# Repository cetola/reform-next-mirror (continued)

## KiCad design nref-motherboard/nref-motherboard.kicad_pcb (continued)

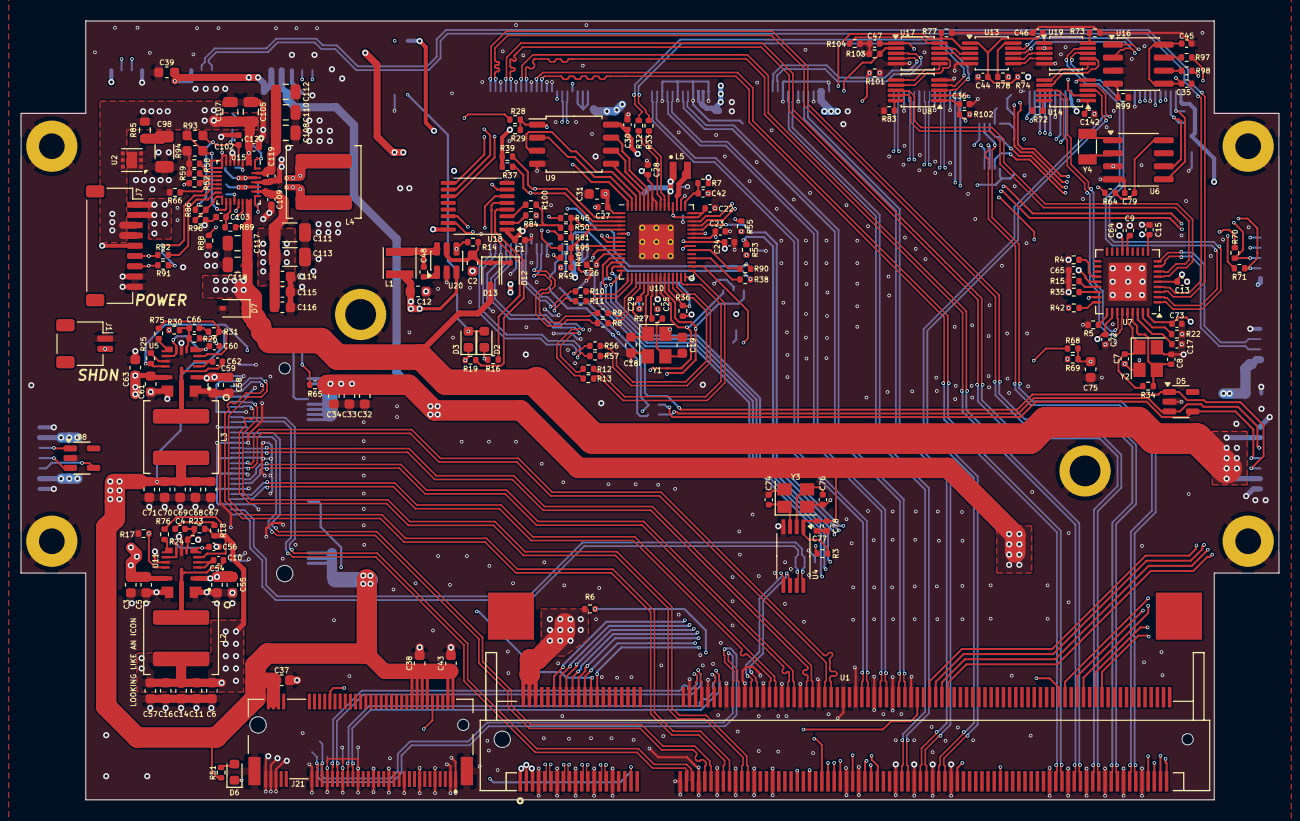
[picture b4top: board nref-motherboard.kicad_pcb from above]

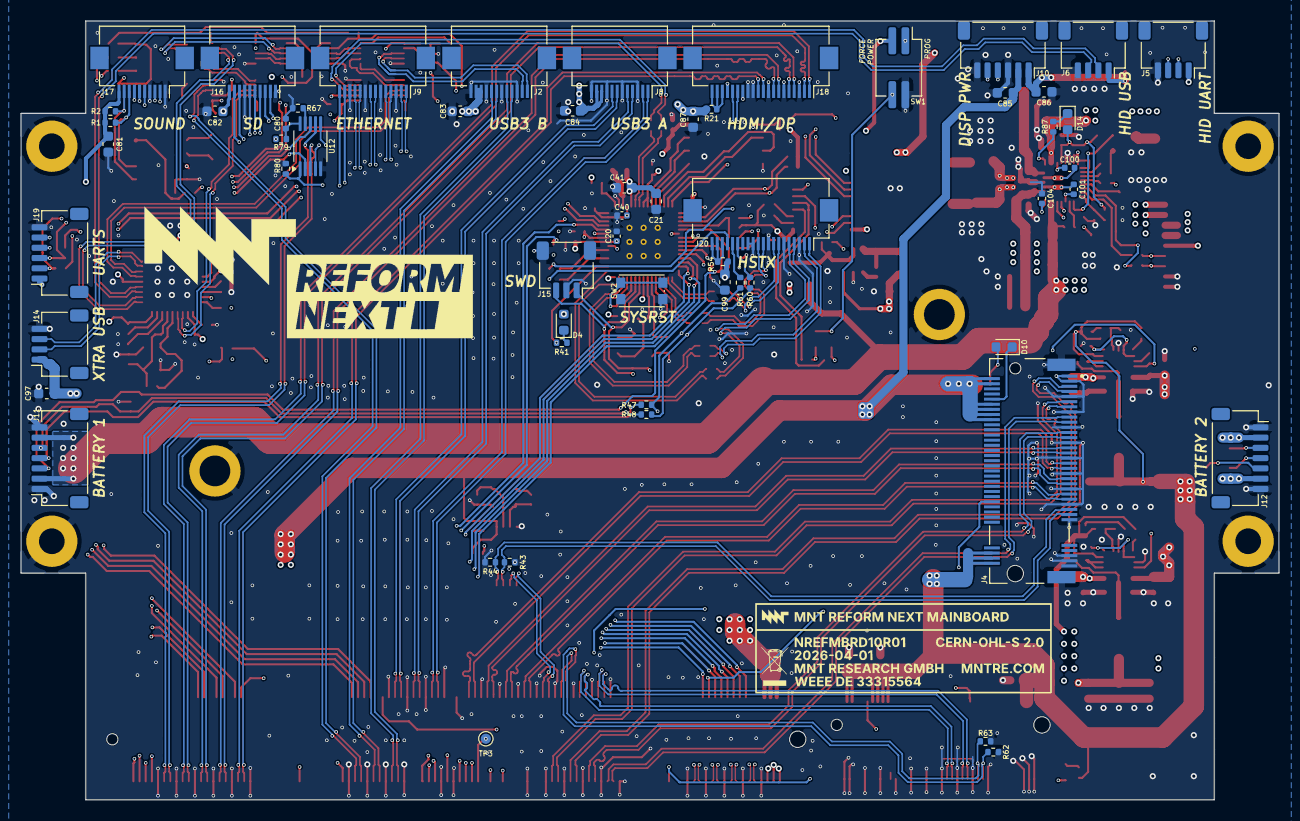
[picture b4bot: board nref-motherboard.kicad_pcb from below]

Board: 6 copper layers, 122.6 x 75.9 mm, 276 parts (60 on the bottom side), 267 nets.

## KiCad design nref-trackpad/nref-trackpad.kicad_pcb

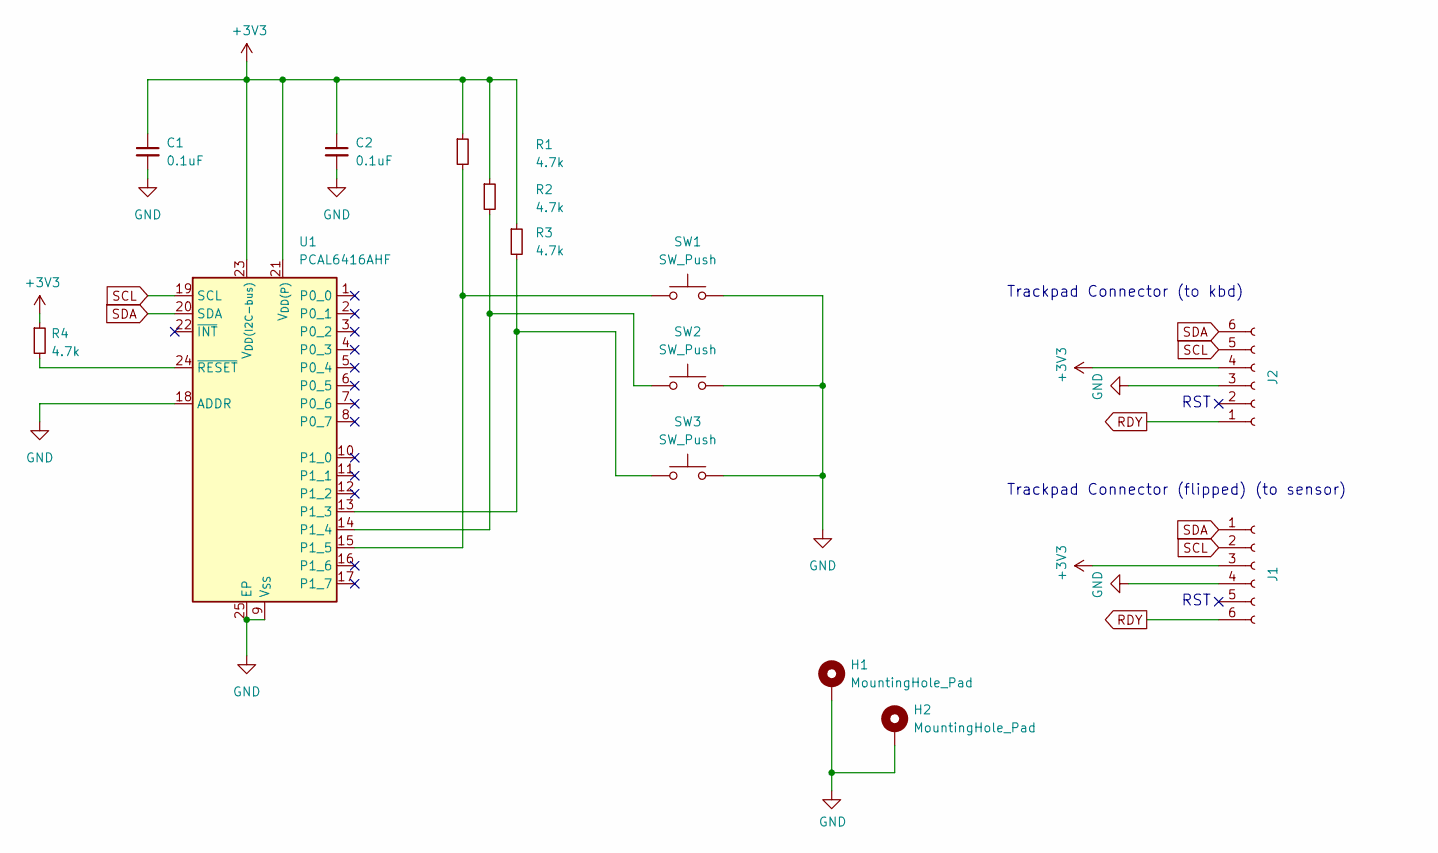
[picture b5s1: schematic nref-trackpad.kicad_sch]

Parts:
C1, C2: 0.1uF; C_0402_1005Metric
H1, H2: MountingHole_Pad; MountingHole_3.2mm_M3_Pad
J1, J2: Conn_01x06_Female; Hirose_FH12-6S-0.5SH_1x06-1MP_P0.50mm_Horizontal; LCSC C202118
R1, R2, R3, R4: 4.7k; R_0402_1005Metric
SW1, SW2, SW3: SW_Push; Cherry_ULP_SMD
U1: PCAL6416AHF; HVQFN-24-1EP_4x4mm_P0.5mm_EP2.1x2.1mm

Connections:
+3V3: C1.1, C2.1, J1.3, J2.4, R1.1, R2.1, R3.1, R4.1, U1.21 (V_{DD(P)}), U1.23 (V_{DD(I2C-bus)})
GND: C1.2, C2.2, H1.1, H2.1, J1.4, J2.3, SW1.2, SW2.2, SW3.2, U1.9 (V_{SS}), U1.18 (ADDR), U1.25 (EP)
unnamed: R3.2, SW3.1, U1.13 (P1_3)
unnamed: R2.2, SW2.1, U1.14 (P1_4)
unnamed: R1.2, SW1.1, U1.15 (P1_5)
unnamed: R4.2, U1.24 (~RESET)
RDY: J1.6, J2.1
SCL: J1.2, J2.5, U1.19 (SCL)
SDA: J1.1, J2.6, U1.20 (SDA)

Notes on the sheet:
Trackpad Connector (to kbd)
RST
Trackpad Connector (flipped) (to sensor)

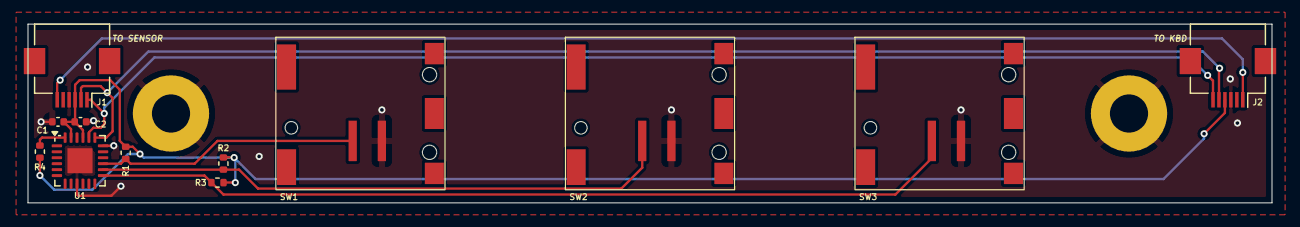
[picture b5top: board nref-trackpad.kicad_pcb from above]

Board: 2 copper layers, 104.4 x 15.0 mm, 14 parts (0 on the bottom side), 9 nets.

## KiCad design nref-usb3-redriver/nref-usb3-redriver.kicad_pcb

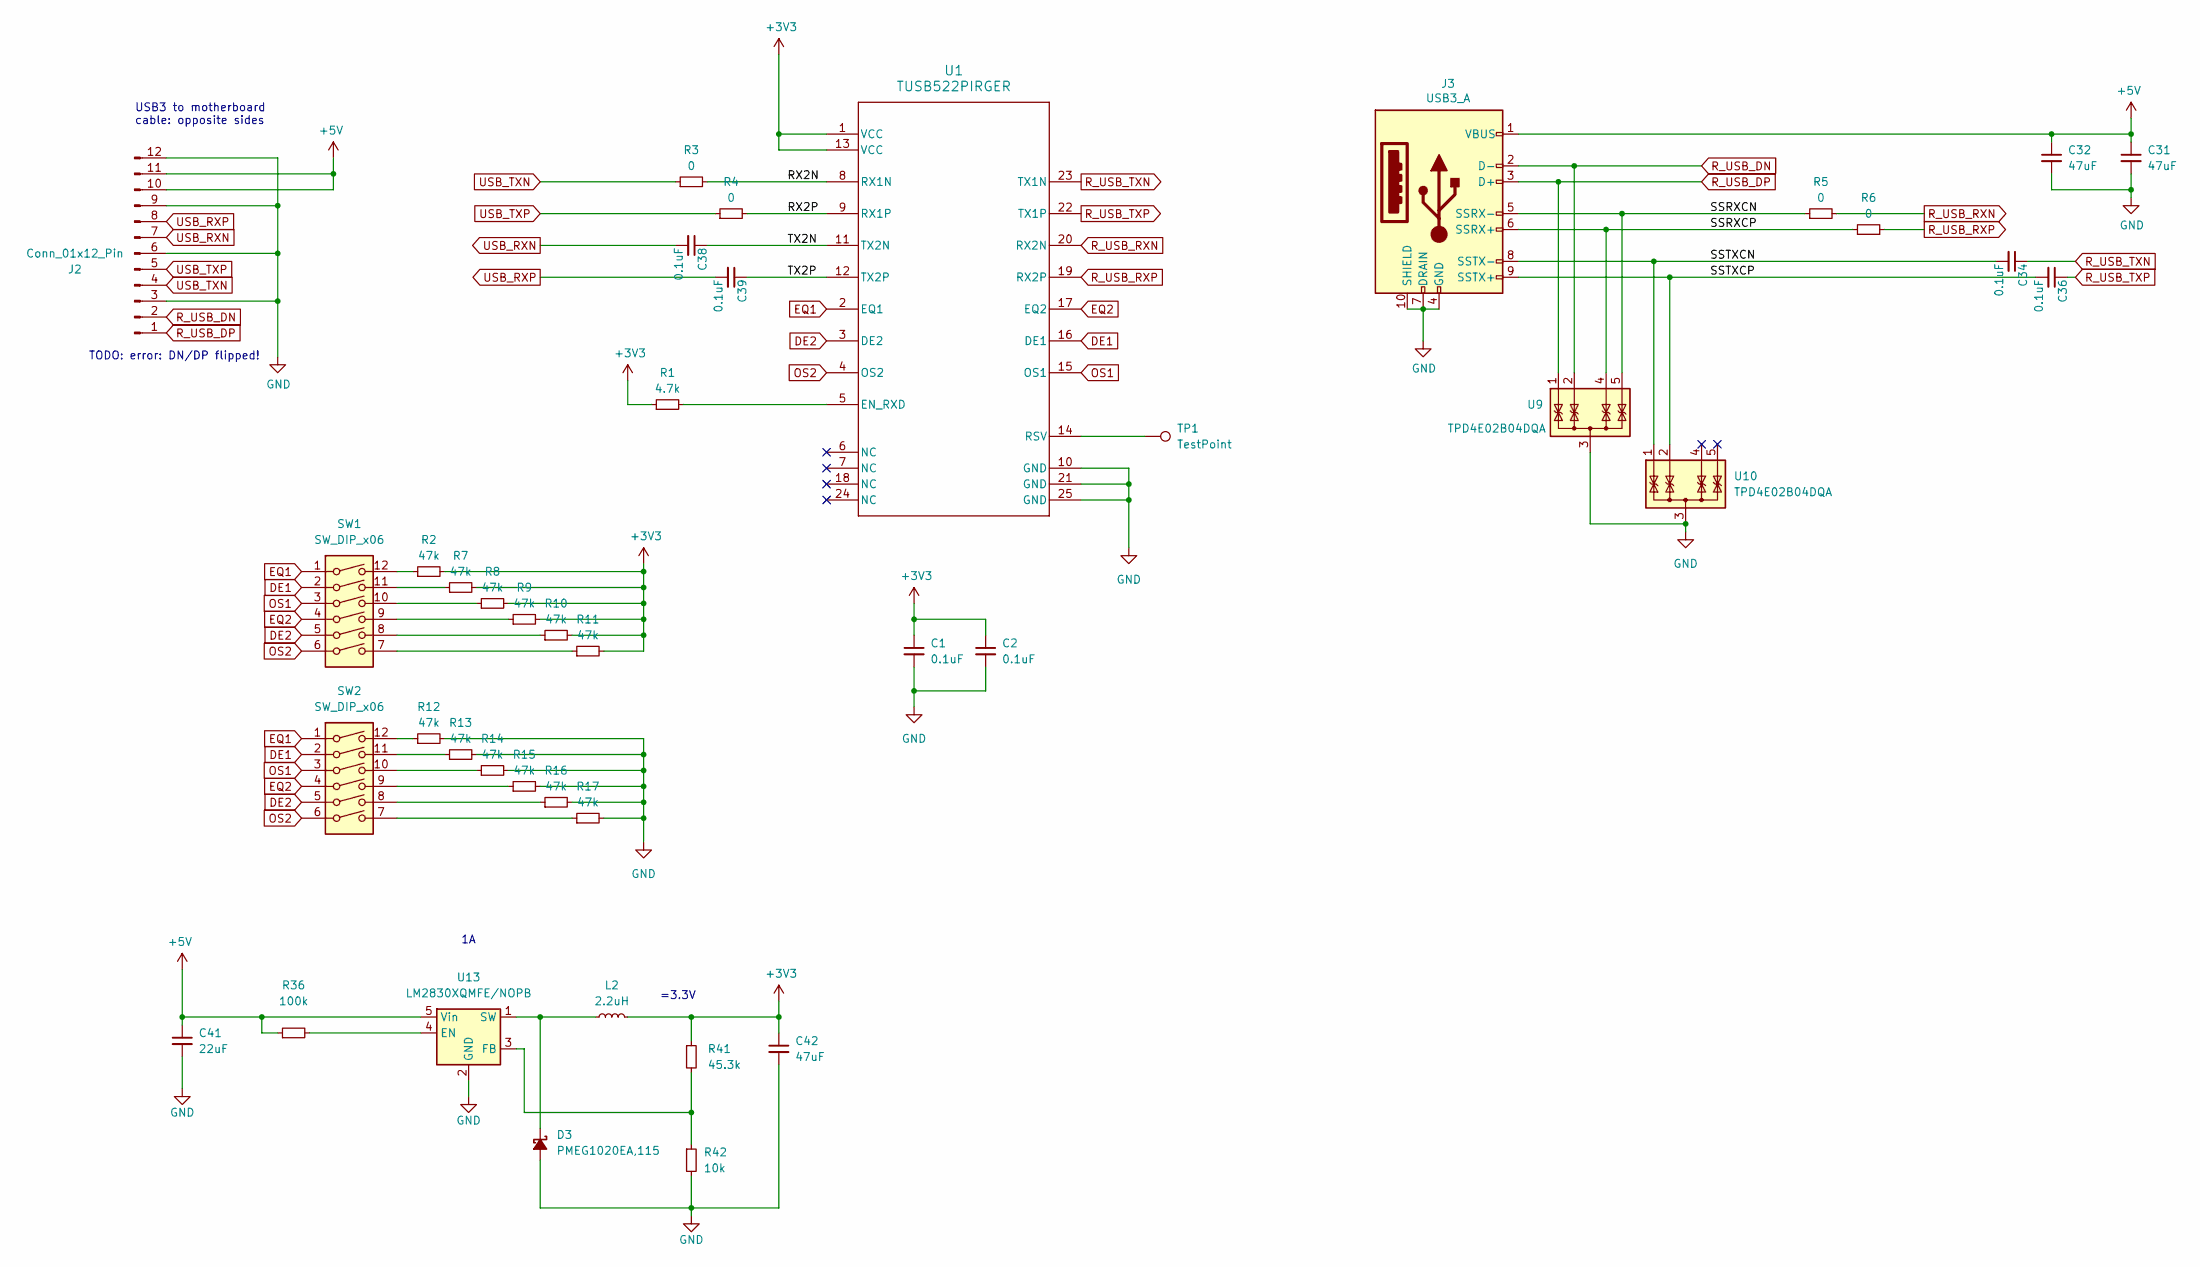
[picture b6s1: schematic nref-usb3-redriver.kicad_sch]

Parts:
C1, C2, C34, C36, C38, C39: 0.1uF; C_0402_1005Metric
C31, C32, C42: 47uF; C_1206_3216Metric
C41: 22uF; C_1206_3216Metric
D3: PMEG1020EA,115; D_SOD-323
J2: Conn_01x12_Pin; Hirose_FH12-12S-0.5SH_1x12-1MP_P0.50mm_Horizontal
J3: USB3_A; USB3_A_Receptacle_Wuerth_692122030100
L2: 2.2uH; L_1210_3225Metric
R1: 4.7k; R_0402_1005Metric
R2, R7, R8, R9, R10, R11, R12, R13, R14, R15, R16, R17: 47k; R_0402_1005Metric
R3, R4, R5, R6: 0; R_0402_1005Metric
R36: 100k; R_0402_1005Metric
R41: 45.3k; R_0402_1005Metric
R42: 10k; R_0402_1005Metric
SW1, SW2: SW_DIP_x06; SW_DIP_SPSTx06_Slide_Omron_A6H-6101_W6.15mm_P1.27mm
TP1: TestPoint; TestPoint_Pad_D1.0mm
U1: TUSB522PIRGER; RGE0024C
U9, U10: TPD4E02B04DQA; USON-10_2.5x1.0mm_P0.5mm
U13: LM2830XQMFE/NOPB; SOT-23-5

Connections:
+3V3: C1.1, C2.1, C42.1, L2.2, R1.1, R2.2, R7.2, R8.2, R9.2, R10.2, R11.2, R41.1, U1.1 (VCC), U1.13 (VCC)
+5V: C31.1, C32.1, C41.1, J2.10, J2.11, J3.1 (VBUS), R36.1, U13.5 (Vin)
/RX2N: R3.2, U1.8 (RX1N)
/RX2P: R4.2, U1.9 (RX1P)
/SSRXCN: J3.5 (SSRX-), R5.1, U9.5 (IO4), U9.6 (IO4)
/SSRXCP: J3.6 (SSRX+), R6.1, U9.4 (IO3), U9.7 (IO3)
/SSTXCN: C34.2, J3.8 (SSTX-), U10.1 (IO1), U10.10 (IO1)
/SSTXCP: C36.2, J3.9 (SSTX+), U10.2 (IO2), U10.9 (IO2)
/TX2N: C38.1, U1.11 (TX2N)
/TX2P: C39.1, U1.12 (TX2P)
DE1: SW1.2, SW2.2, U1.16 (DE1)
DE2: SW1.5, SW2.5, U1.3 (DE2)
EQ1: SW1.1, SW2.1, U1.2 (EQ1)
EQ2: SW1.4, SW2.4, U1.17 (EQ2)
GND: C1.2, C2.2, C31.2, C32.2, C41.2, C42.2, D3.2 (A), J2.3, J2.6, J2.9, J2.12, J3.4 (GND), J3.7 (DRAIN), J3.10 (SHIELD), R12.2, R13.2, R14.2, R15.2, R16.2, R17.2, R42.2, U1.10 (GND), U1.21 (GND), U1.25 (GND), U9.3 (G), U9.8 (G), U10.3 (G), U10.8 (G), U13.2 (GND)
unnamed: D3.1 (K), L2.1, U13.1 (SW)
unnamed: R2.1, SW1.12
unnamed: R7.1, SW1.11
unnamed: R8.1, SW1.10
unnamed: R9.1, SW1.9
unnamed: R10.1, SW1.8
unnamed: R11.1, SW1.7
unnamed: R12.1, SW2.12
unnamed: R13.1, SW2.11
unnamed: R14.1, SW2.10
unnamed: R15.1, SW2.9
unnamed: R16.1, SW2.8
unnamed: R17.1, SW2.7
unnamed: R1.2, U1.5 (EN_RXD)
unnamed: TP1.1, U1.14 (RSV)
unnamed: R36.2, U13.4 (EN)
unnamed: R41.2, R42.1, U13.3 (FB)
OS1: SW1.3, SW2.3, U1.15 (OS1)
OS2: SW1.6, SW2.6, U1.4 (OS2)
R_USB_DN: J2.2, J3.2 (D-), U9.2 (IO2), U9.9 (IO2)
R_USB_DP: J2.1, J3.3 (D+), U9.1 (IO1), U9.10 (IO1)
R_USB_RXN: R5.2, U1.20 (RX2N)
R_USB_RXP: R6.2, U1.19 (RX2P)
R_USB_TXN: C34.1, U1.23 (TX1N)
R_USB_TXP: C36.1, U1.22 (TX1P)
USB_RXN: C38.2, J2.7
USB_RXP: C39.2, J2.8
USB_TXN: J2.4, R3.1
USB_TXP: J2.5, R4.1

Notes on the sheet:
TODO: error: DN/DP flipped!
=3.3V
USB3 to motherboard cable: opposite sides

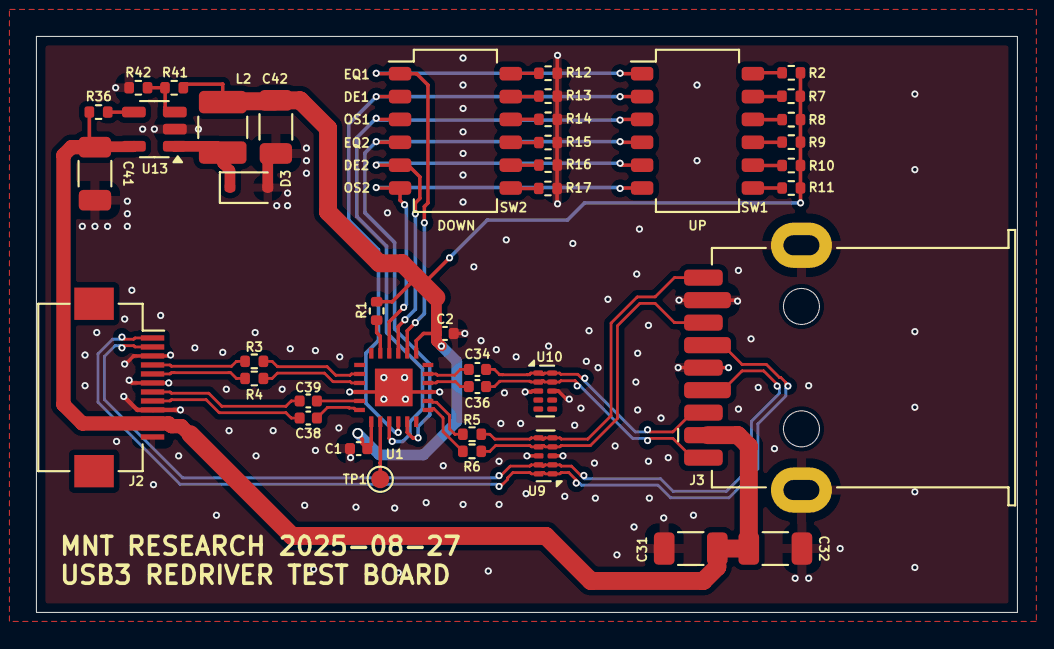
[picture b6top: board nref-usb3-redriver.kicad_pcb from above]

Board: 4 copper layers, 54.5 x 32.0 mm, 41 parts (0 on the bottom side), 44 nets.

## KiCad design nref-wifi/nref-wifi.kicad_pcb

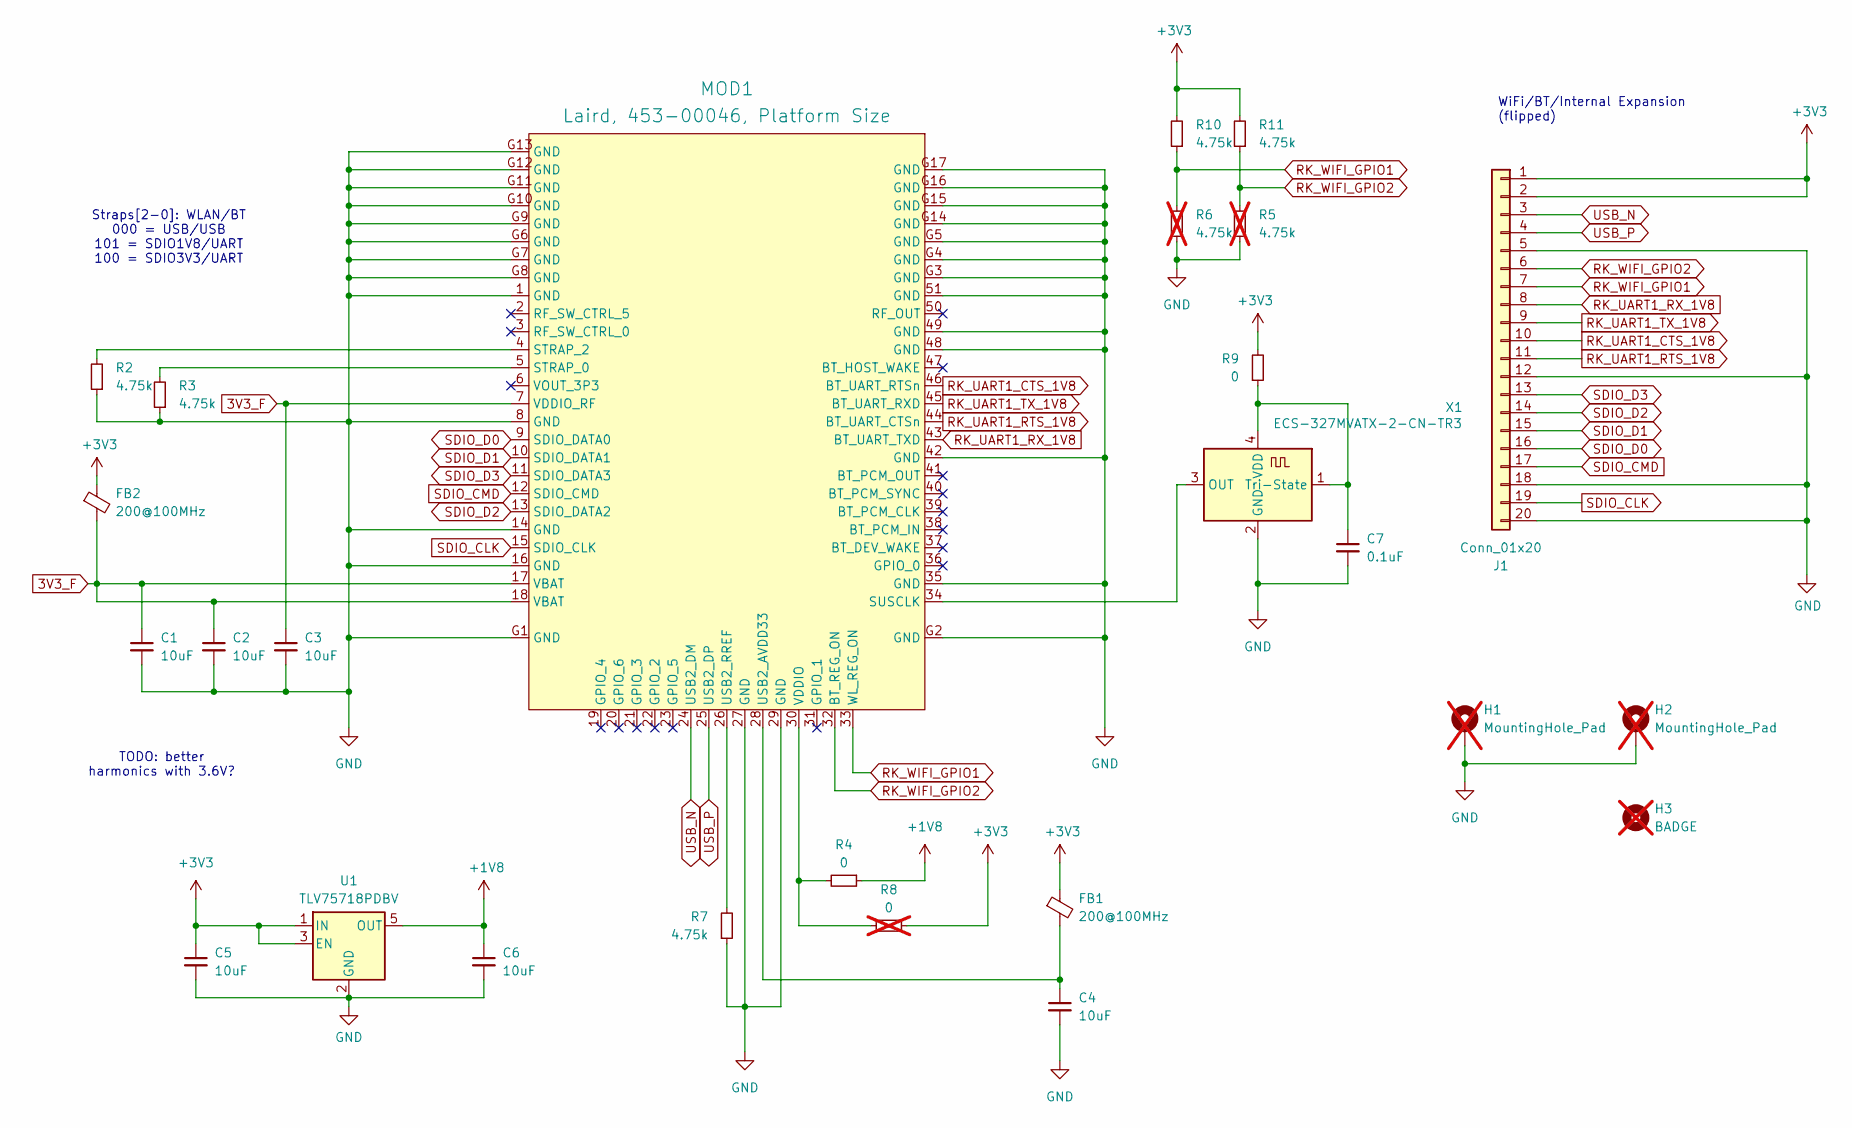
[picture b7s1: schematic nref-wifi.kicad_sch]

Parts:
C1, C2, C3, C4, C5, C6: 10uF; C_0603_1608Metric
C7: 0.1uF; C_0603_1608Metric
FB1, FB2: 200@100MHz; L_0603_1608Metric
H1, H2: MountingHole_Pad; MountingHole_2.2mm_M2_Pad; not fitted
H3: BADGE; nref-wifi-badge; not fitted
J1: Conn_01x20; Hirose_FH12-20S-0.5SH_1x20-1MP_P0.50mm_Horizontal
MOD1: Laird, 453-00046, Platform Size; Laird, Sterling LWB5+ Module, Platform Side
R2, R3, R7, R10, R11: 4.75k; R_0603_1608Metric
R4, R9: 0; R_0603_1608Metric
R5, R6: 4.75k; R_0603_1608Metric; not fitted
R8: 0; R_0603_1608Metric; not fitted
U1: TLV75718PDBV; SOT-23-5
X1: ECS-327MVATX-2-CN-TR3; Oscillator_SMD_ECS_2520MV-xxx-xx-4Pin_2.5x2.0mm

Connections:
3V3_F: C1.1, C2.1, C3.1, FB2.2, MOD1.7 (VDDIO_RF), MOD1.17 (VBAT), MOD1.18 (VBAT)
+1V8: C6.1, R4.1, U1.5 (OUT)
+3V3: C5.1, FB1.1, FB2.1, J1.1, J1.2, R8.1, R9.2, R10.2, R11.2, U1.1 (IN), U1.3 (EN)
GND: C1.2, C2.2, C3.2, C4.2, C5.2, C6.2, C7.2, H1.1, H2.1, J1.5, J1.12, J1.18, J1.20, MOD1.1 (GND), MOD1.8 (GND), MOD1.14 (GND), MOD1.16 (GND), MOD1.27 (GND), MOD1.29 (GND), MOD1.35 (GND), MOD1.42 (GND), MOD1.48 (GND), MOD1.49 (GND), MOD1.51 (GND), MOD1.G1 (GND), MOD1.G2 (GND), MOD1.G3 (GND), MOD1.G4 (GND), MOD1.G5 (GND), MOD1.G6 (GND), MOD1.G7 (GND), MOD1.G8 (GND), MOD1.G9 (GND), MOD1.G10 (GND), MOD1.G11 (GND), MOD1.G12 (GND), MOD1.G13 (GND), MOD1.G14 (GND), MOD1.G15 (GND), MOD1.G16 (GND), MOD1.G17 (GND), R2.1, R3.1, R5.1, R6.1, R7.1, U1.2 (GND), X1.2 (GND)
unnamed: MOD1.5 (STRAP_0), R3.2
unnamed: MOD1.4 (STRAP_2), R2.2
unnamed: MOD1.34 (SUSCLK), X1.3 (OUT)
unnamed: C4.1, FB1.2, MOD1.28 (USB2_AVDD33)
unnamed: MOD1.26 (USB2_RREF), R7.2
unnamed: MOD1.30 (VDDIO), R4.2, R8.2
unnamed: C7.1, R9.1, X1.1 (Tri-State), X1.4 (VDD)
RK_UART1_CTS_1V8: J1.10, MOD1.46 (BT_UART_RTSn)
RK_UART1_RTS_1V8: J1.11, MOD1.44 (BT_UART_CTSn)
RK_UART1_RX_1V8: J1.8, MOD1.43 (BT_UART_TXD)
RK_UART1_TX_1V8: J1.9, MOD1.45 (BT_UART_RXD)
RK_WIFI_GPIO1: J1.7, MOD1.33 (WL_REG_ON), R6.2, R10.1
RK_WIFI_GPIO2: J1.6, MOD1.32 (BT_REG_ON), R5.2, R11.1
SDIO_CLK: J1.19, MOD1.15 (SDIO_CLK)
SDIO_CMD: J1.17, MOD1.12 (SDIO_CMD)
SDIO_D0: J1.16, MOD1.9 (SDIO_DATA0)
SDIO_D1: J1.15, MOD1.10 (SDIO_DATA1)
SDIO_D2: J1.14, MOD1.13 (SDIO_DATA2)
SDIO_D3: J1.13, MOD1.11 (SDIO_DATA3)
USB_N: J1.3, MOD1.24 (USB2_DM)
USB_P: J1.4, MOD1.25 (USB2_DP)

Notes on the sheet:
WiFi/BT/Internal Expansion (flipped)
Straps[2-0]: WLAN/BT 000 = USB/USB 101 = SDIO1V8/UART 100 = SDIO3V3/UART
TODO: better harmonics with 3.6V?

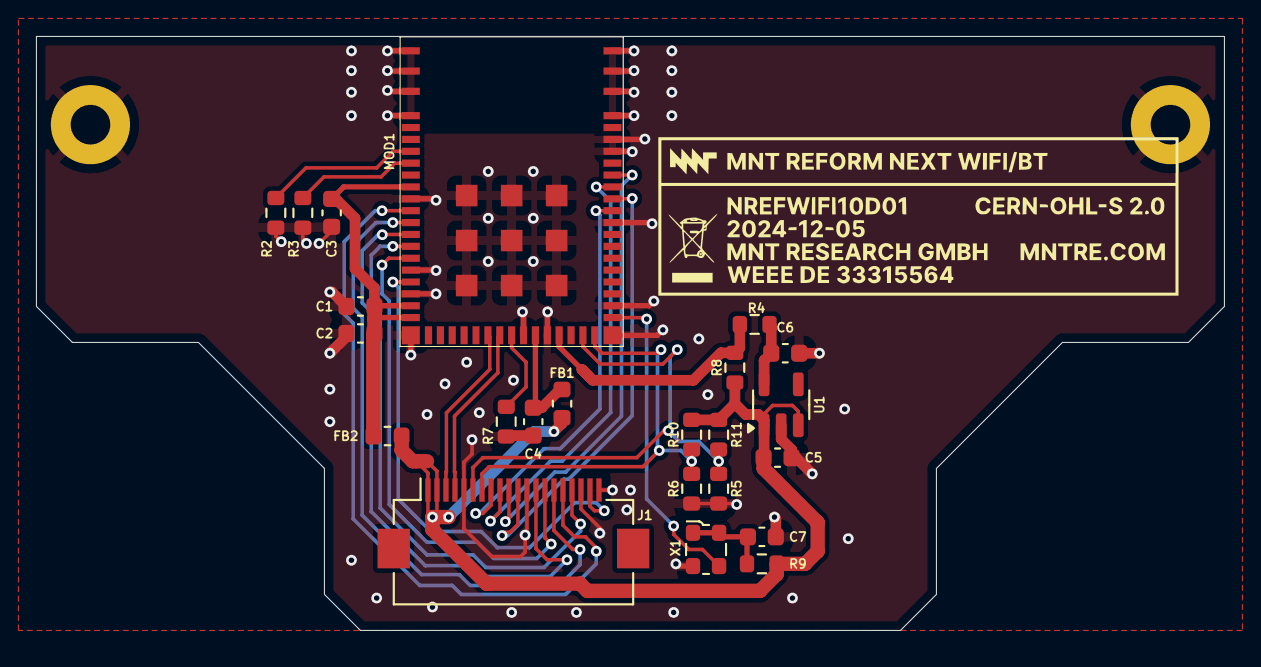
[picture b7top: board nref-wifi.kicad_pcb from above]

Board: 2 copper layers, 66.0 x 33.0 mm, 26 parts (0 on the bottom side), 25 nets.
